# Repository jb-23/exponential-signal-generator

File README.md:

# Exponential Step Signal Generator

This circuit generates a fixed waveform of exponentially rising DC steps, which
could be used for testing logarithmic amplifiers.

Output voltages range from 320 uV to 3.2V in steps with a ratio of 3.16,
equivalent to a 10 dB change. The waveform repeats at a nominal 50 Hz to allow
a flicker-free image on an analogue oscilloscope.

The PCB is designed to work as a naked board that sits on top of the 9V battery
that powers it. The output pads are designed to accept the majority of 4mm
binding posts and when unpopulated will also work with crocodile clips.

The circuit has been laid out primarily in surface mount components; as a
concession to the robustness requirements of the designer, through hole
components are used for the trimmer resistors and the power switch. Further the
trimmer resistor positions will accept components with either staggered or
in-line legs, the former being preferred for mechanical stability.

Multiple footprints for the voltage regulator are provided as a convenience
to accomodate the limited availability of less common negative 5V LDO regulators
required by this design; only one of the options should be fitted.

Resistor R33 can be either a surface mount or through hole component as
is convenient, any value in the range 100 - 150 ohms being adequate if the
preferred value is not available. Higher values will decrease the output drive
capability for the highest voltage steps.

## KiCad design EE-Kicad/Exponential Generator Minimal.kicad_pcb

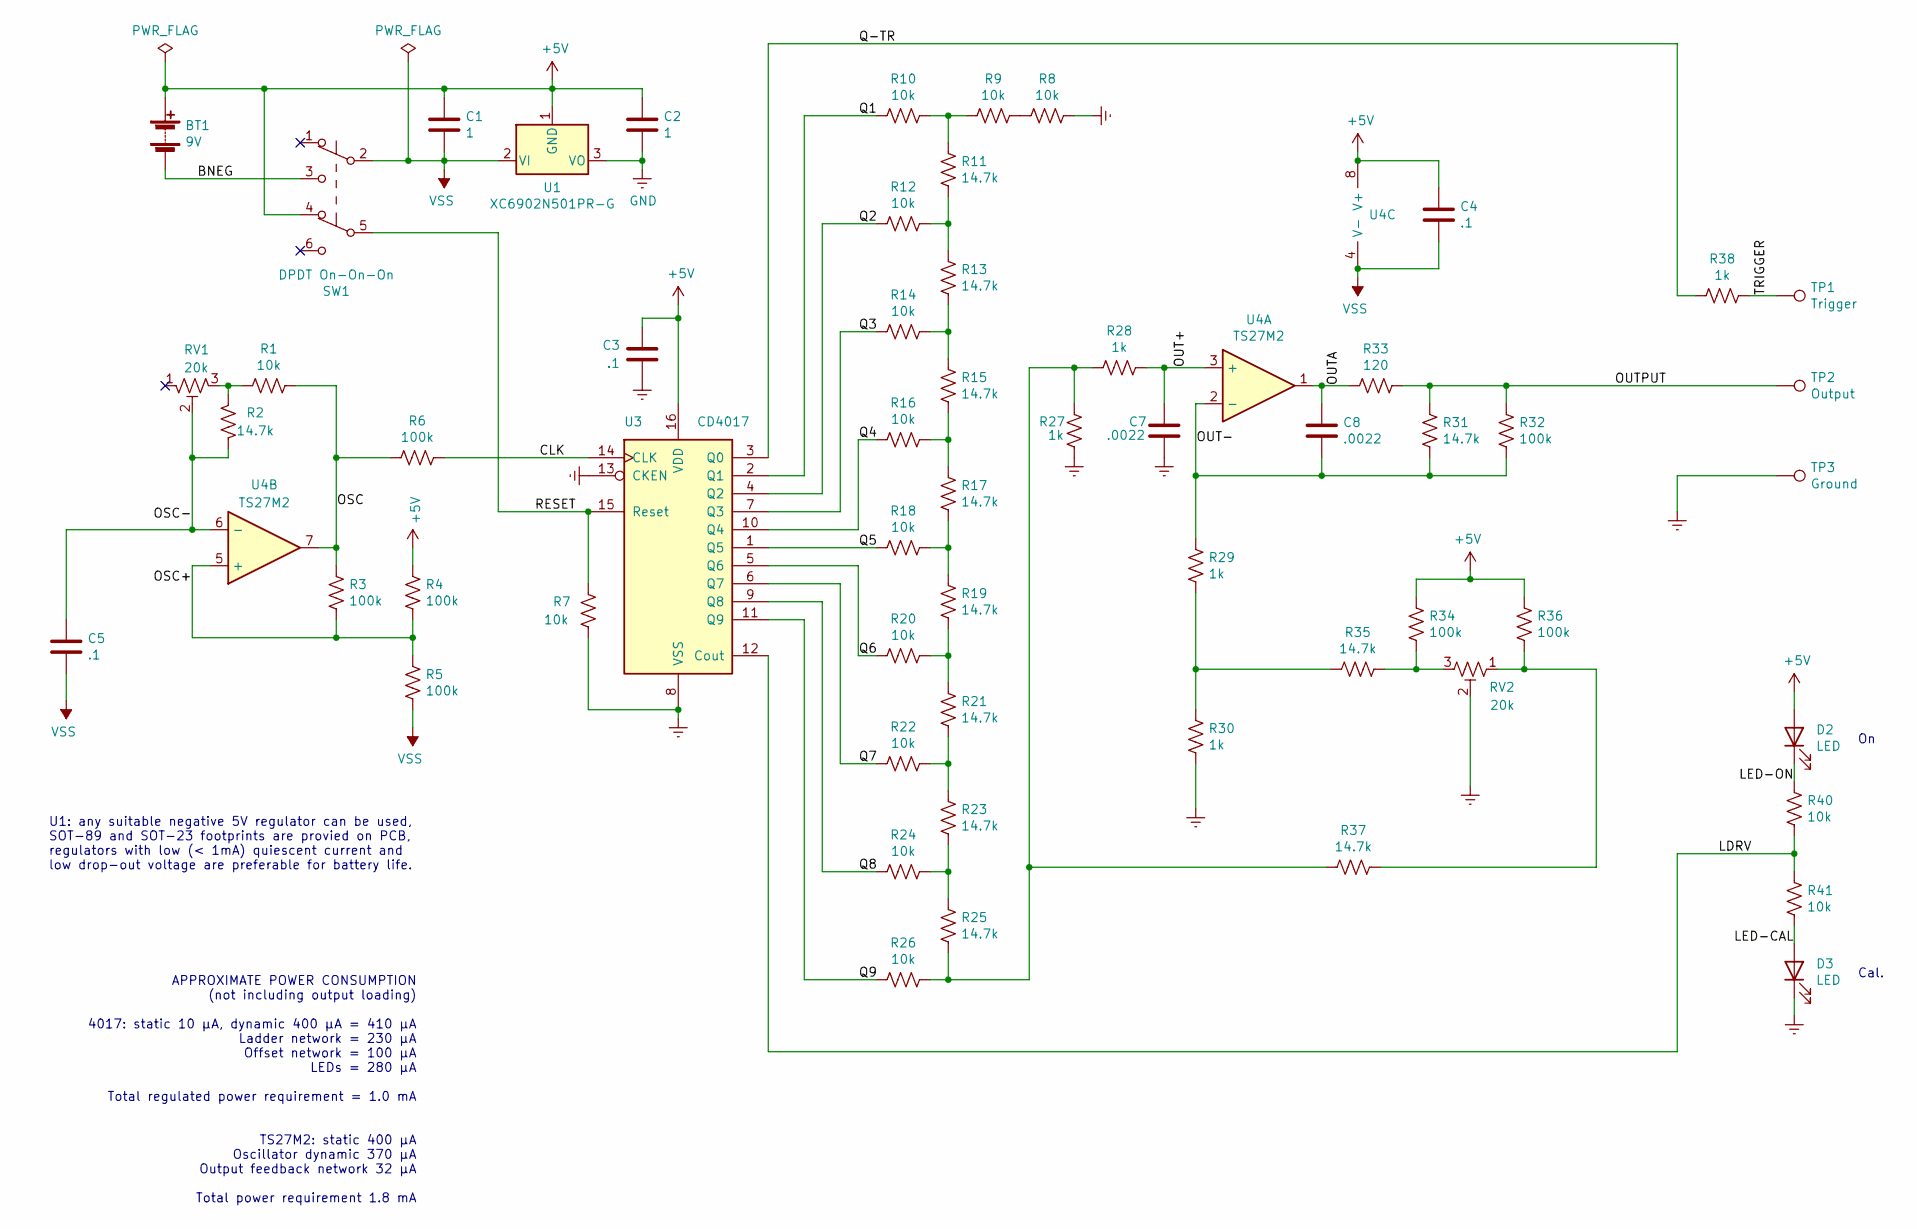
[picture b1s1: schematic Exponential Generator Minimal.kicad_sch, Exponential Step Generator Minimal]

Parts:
BT1: 9V; BatteryHolder_PCB_PP3
C1, C2: 1; C_1206_3216Metric_Pad1.33x1.80mm_HandSolder
C3, C4, C5: .1; C_1206_3216Metric_Pad1.33x1.80mm_HandSolder
C7, C8: .0022; C_0805_2012Metric_Pad1.18x1.45mm_HandSolder
D2, D3: LED; LED_0805_2012Metric_Pad1.15x1.40mm_HandSolder
R1, R7, R8, R9, R10, R12, R14, R16, R18, R20, R22, R24, R26, R40, R41: 10k; R_0805_2012Metric_Pad1.20x1.40mm_HandSolder
R2, R11, R13, R15, R17, R19, R21, R23, R25, R31, R35, R37: 14.7k; R_0805_2012Metric_Pad1.20x1.40mm_HandSolder
R3, R4, R5, R6, R32, R34, R36: 100k; R_0805_2012Metric_Pad1.20x1.40mm_HandSolder
R27, R28, R29, R30, R38: 1k; R_0805_2012Metric_Pad1.20x1.40mm_HandSolder
R33: 120; R_Axial_DIN0207_L6.3mm_D2.5mm_P10.16mm_Horizontal
RV1, RV2: 20k; Trimmer_Universal_3296_Horizontal
SW1: DPDT On-On-On; Switch_Toggle_DPDT_RA_PCB
TP1: Trigger; Binding_Post
TP2: Output; Binding_Post
TP3: Ground; Binding_Post
U1: XC6902N501PR-G; SOT-89-3_Handsoldering
U3: CD4017; SOIC-16_3.9x9.9mm_P1.27mm
U4: TS27M2; SOIC-8_3.9x4.9mm_P1.27mm

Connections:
+5V: BT1.1 (+), C1.1, C2.1, C3.1, C4.1, D2.2 (A), R4.1, R34.1, R36.1, SW1.4 (A), U1.1 (GND), U3.16 (VDD), U4.8 (V+)
/BNEG: BT1.2 (-), SW1.3 (C)
/CLK: R6.1, U3.14 (CLK)
/LDRV: R40.2, R41.1, U3.12 (Cout)
/LED-CAL: D3.2 (A), R41.2
/LED-ON: D2.1 (K), R40.1
/OSC: R1.1, R3.1, R6.2, U4.7
/OSC+: R3.2, R4.2, R5.1, U4.5 (+)
/OSC-: C5.1, R2.2, RV1.2, U4.6 (-)
/OUT+: C7.1, R28.1, U4.3 (+)
/OUT-: C8.2, R29.1, R31.2, R32.2, U4.2 (-)
/OUTA: C8.1, R33.2, U4.1; also elsewhere on the board
/OUTPUT: R31.1, R32.1, R33.1, TP2.1; also elsewhere on the board
/Q1: R10.2, U3.2 (Q1)
/Q2: R12.2, U3.4 (Q2)
/Q3: R14.2, U3.7 (Q3)
/Q4: R16.2, U3.10 (Q4)
/Q5: R18.2, U3.1 (Q5)
/Q6: R20.2, U3.5 (Q6)
/Q7: R22.2, U3.6 (Q7)
/Q8: R24.2, U3.9 (Q8)
/Q9: R26.2, U3.11 (Q9)
/Q-TR: R38.2, U3.3 (Q0)
/RESET: R7.1, SW1.5 (B), U3.15 (Reset)
/TRIGGER: R38.1, TP1.1
GND: C2.2, C3.2, C7.2, D3.1 (K), R7.2, R8.1, R27.2, R30.2, RV2.2, TP3.1, U1.3 (VO), U3.8 (VSS), U3.13 (CKEN)
unnamed: R1.2, R2.1, RV1.3
unnamed: R8.2, R9.1
unnamed: R9.2, R10.1, R11.1
unnamed: R11.2, R12.1, R13.1
unnamed: R13.2, R14.1, R15.1
unnamed: R15.2, R16.1, R17.1
unnamed: R17.2, R18.1, R19.1
unnamed: R19.2, R20.1, R21.1
unnamed: R21.2, R22.1, R23.1
unnamed: R23.2, R24.1, R25.1
unnamed: R25.2, R26.1, R27.1, R28.2, R37.2
unnamed: R29.2, R30.1, R35.2
unnamed: R34.2, R35.1, RV2.3
unnamed: R36.2, R37.1, RV2.1
VSS: C1.2, C4.2, C5.2, R5.2, SW1.2 (B), U1.2 (VI), U4.4 (V-)

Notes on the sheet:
Cal.
APPROXIMATE POWER CONSUMPTION (not including output loading) 4017: static 10 µA, dynamic 400 µA = 410 µA Ladder network = 230 µA Offset network = 100 µA LEDs = 280 µA Total regulated power requirement = 1.0 mA TS27M2: static 400 µA Oscillator dynamic 370 µA Output feedback network 32 µA Total power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
U1: any suitable negative 5V regulator can be used, SOT-89 and SOT-23 footprints are provied on PCB, regulators with low (< 1mA) quiescent current and low drop-out voltage are preferable for battery life.

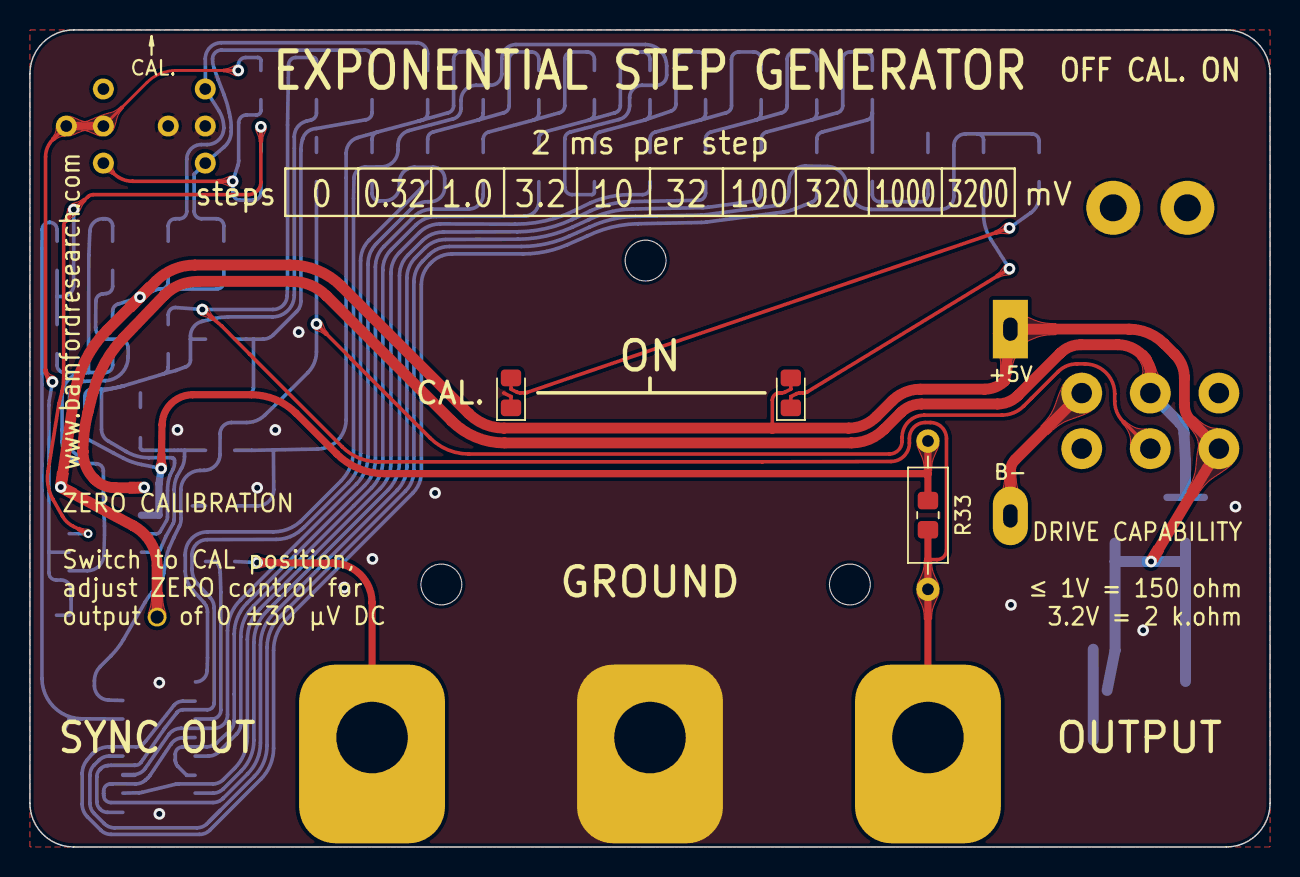
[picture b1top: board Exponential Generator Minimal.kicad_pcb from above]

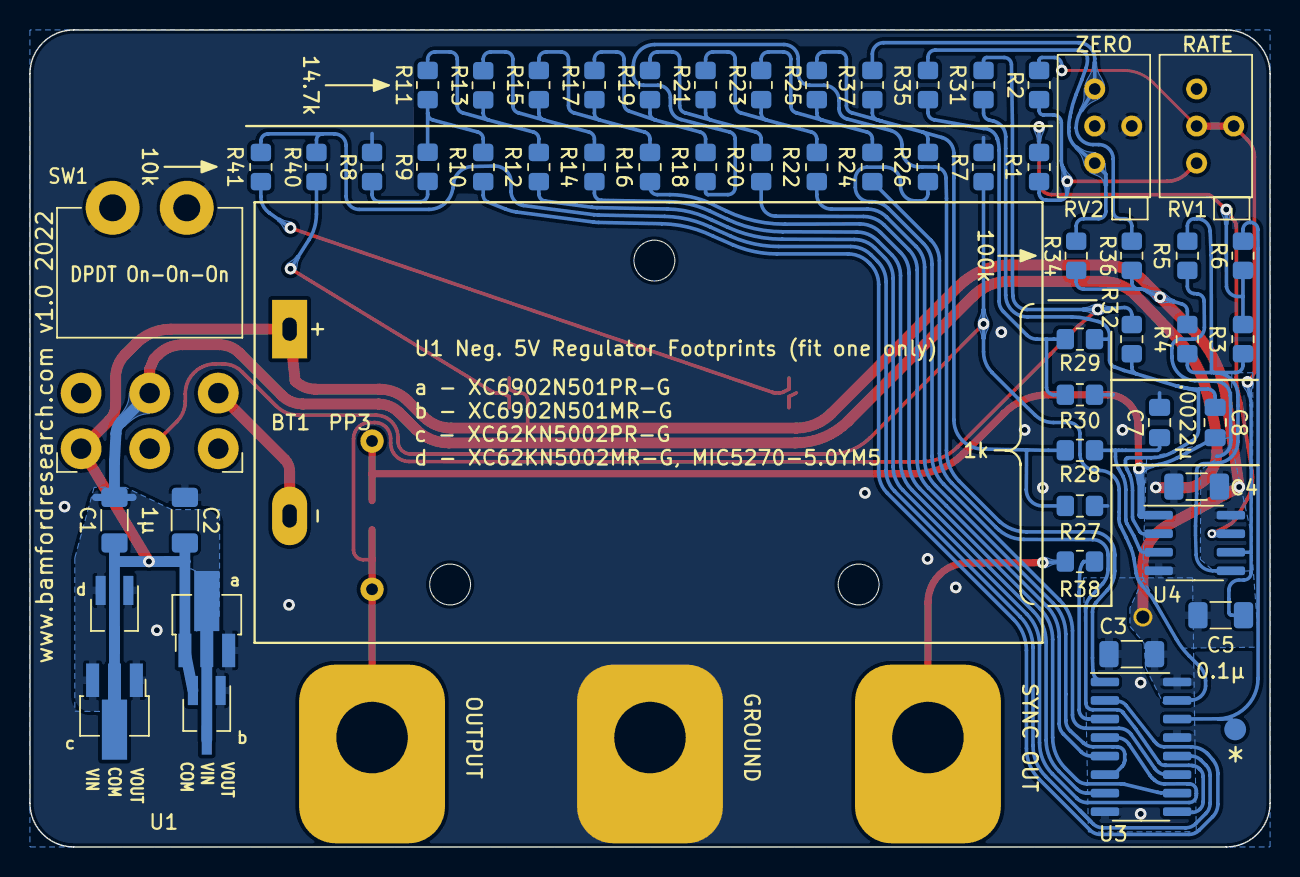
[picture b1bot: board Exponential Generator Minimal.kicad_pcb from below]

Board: 2 copper layers, 85.0 x 56.0 mm, 60 parts (53 on the bottom side), 41 nets.

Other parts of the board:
R33#2: 120; R_0805_2012Metric_Pad1.20x1.40mm_HandSolder

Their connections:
/OUTA: R33#2.2; also elsewhere on the board
/OUTPUT: R33#2.1; also elsewhere on the board

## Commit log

2022-03-05 Version 1.0
